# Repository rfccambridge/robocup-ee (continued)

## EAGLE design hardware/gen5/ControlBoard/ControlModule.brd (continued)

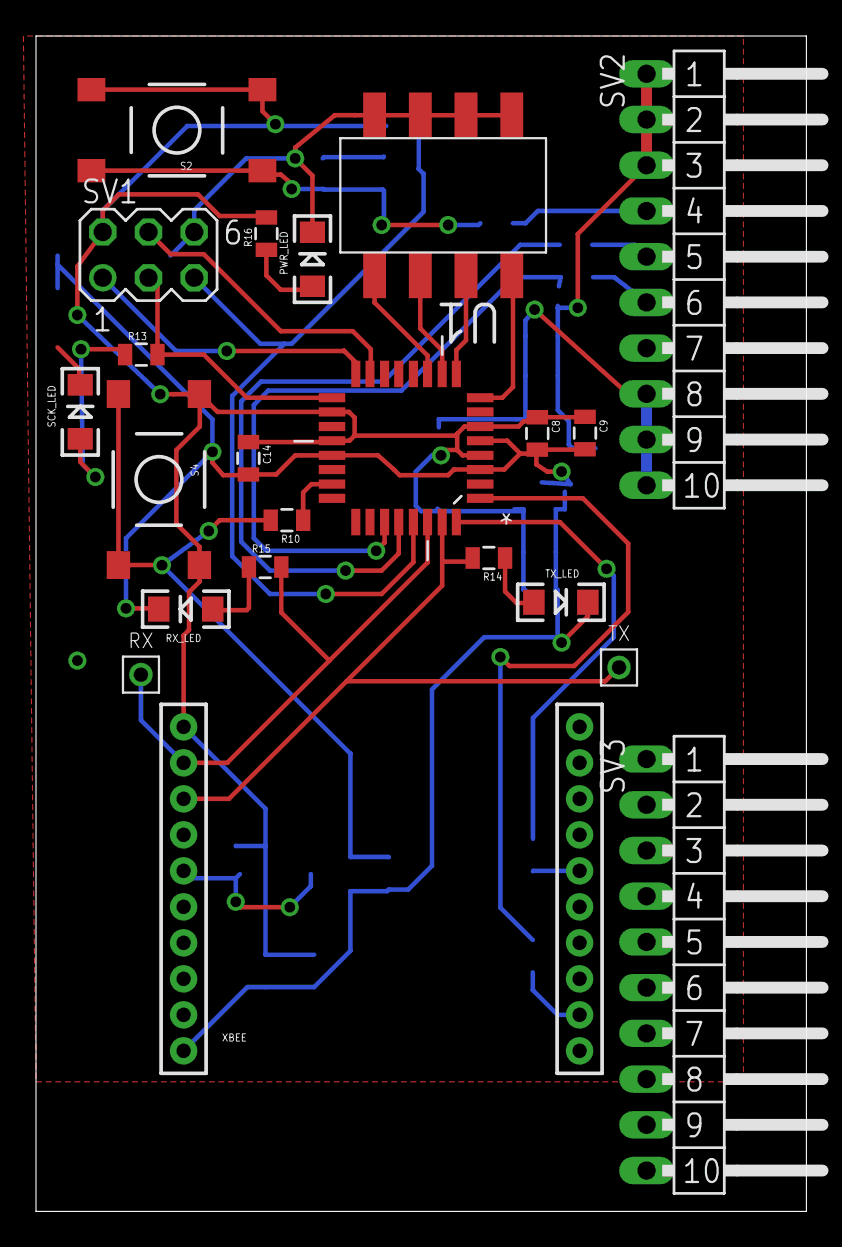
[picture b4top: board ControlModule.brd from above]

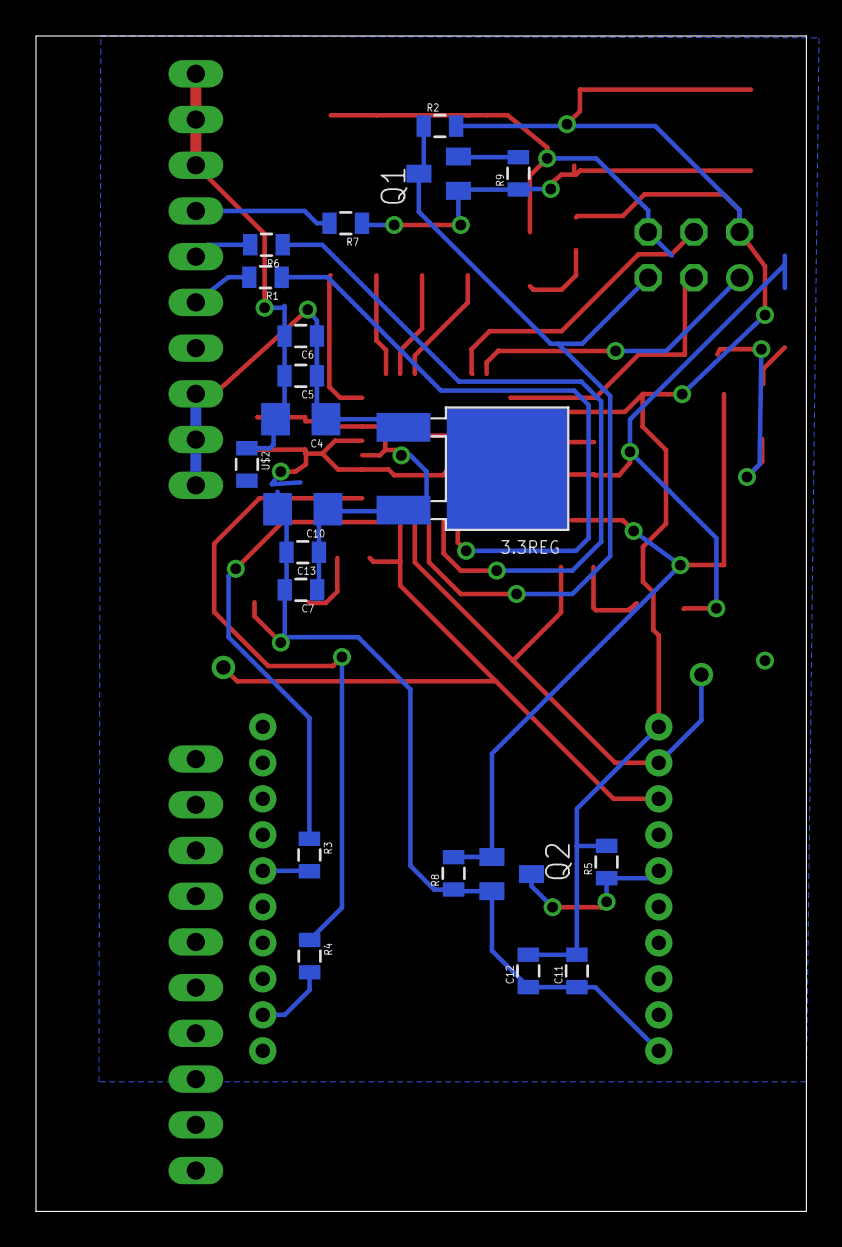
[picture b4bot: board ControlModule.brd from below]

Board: 2 copper layers, 42.8 x 65.3 mm, 44 parts (21 on the bottom side), 31 nets.

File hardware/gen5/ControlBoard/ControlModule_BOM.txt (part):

Partlist exported from C:/Users/joncr_000/robocup/robocup-ee/hardware/gen5/ControlBoard/ControlModule.sch at 12/26/2016 15:41:58

Part    Value         Device           Package               Description                                             MF MPN           OC_FARNELL OC_NEWARK PACKAGE PROD_ID    SUPPLIER VALUE        
3.3REG  3.3REG1AREG   3.3REG1AREG      DPAK                                                                                                                                                         
C4      47uF          CAP1206          1206                  Capacitor                                                                                                                              
C5      1uF           CAP0805          0805                  Capacitor                                                                                                                              
C6      0.01uF        CAP0805          0805                  Capacitor                                                                                                                              
C7      0.01uF        CAP0805          0805                  Capacitor                                                                                                                              
C8      10uF          CAP0805          0805                  Capacitor                                                                                                                              
C9      0.1uF         CAP0805          0805                  Capacitor                                                                                                                              
C10     47uF          CAP1206          1206                  Capacitor                                                                                                                              
C11     0.01uF        CAP0805          0805                  Capacitor                                                                                                                              
C12     1uF           CAP0805          0805                  Capacitor                                                                                                                              
C13     1uF           CAP0805          0805                  Capacitor                                                                                                                              
C14     0.1uF         CAP0805          0805                  Capacitor                                                                                                                              
FRAME1  FRAME-LETTER  FRAME-LETTER     CREATIVE_COMMONS      Schematic Frame                                                                                                                        
PWR_LED               LED1206          LED-1206              LEDs                                                                                                                                   
Q1      BSS123        BSS123           SOT23                 N-CHANNEL MOS FET                                                                                                                      
Q2      BSS123        BSS123           SOT23                 N-CHANNEL MOS FET                                                                                                                      
R1      100           RESISTOR0805-RES 0805                  Resistor                                                                                                                               
R2      10k           RESISTOR0805-RES 0805                  Resistor                                                                                                                               
R3      0             RESISTOR0805-RES 0805                  Resistor                                                                                                                               
R4      0             RESISTOR0805-RES 0805                  Resistor                                                                                                                               
R5      10k           RESISTOR0805-RES 0805                  Resistor                                                                                                                               
R6      100           RESISTOR0805-RES 0805                  Resistor                                                                                                                               
R7      100           RESISTOR0805-RES 0805                  Resistor                                                                                                                               
R8      10k           RESISTOR0805-RES 0805                  Resistor                                                                                                                               
R9      10k           RESISTOR0805-RES 0805                  Resistor                                                                                                                               
R10     100           RESISTOR0805-RES 0805                  Resistor                                                                                                                               
R13     1k            RESISTOR0805-RES 0805                  Resistor                                                                                                                               
R14     1k            RESISTOR0805-RES 0805                  Resistor                                                                                                                               
R15     1k            RESISTOR0805-RES 0805                  Resistor                                                                                                                               
R16     1k            RESISTOR0805-RES 0805                  Resistor                                                                                                                               
RX      TEST_PT       TEST_PT          TESTING_PT            Testing Point                                                                                                                          
RX_LED                LED1206          LED-1206              LEDs                                                                                                                                   
S2      TAC_SWITCHSMD TAC_SWITCHSMD    TACTILE-SWITCH-SMD    Momentary Switch                                                                                      SWCH-08247          TAC_SWITCHSMD
S4      TAC_SWITCHSMD TAC_SWITCHSMD    TACTILE-SWITCH-SMD    Momentary Switch                                                                                      SWCH-08247          TAC_SWITCHSMD
SCK_LED               LED1206          LED-1206              LEDs                                                                                                                                   
SV1     ICSP          MA03-2           MA03-2                PIN HEADER                                                               unknown    unknown                                            
SV2                   MA10-1W          MA10-1W               PIN HEADER                                                               unknown    unknown                                            
SV3                   MA10-1W          MA10-1W               PIN HEADER                                                               unknown    unknown                                            
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
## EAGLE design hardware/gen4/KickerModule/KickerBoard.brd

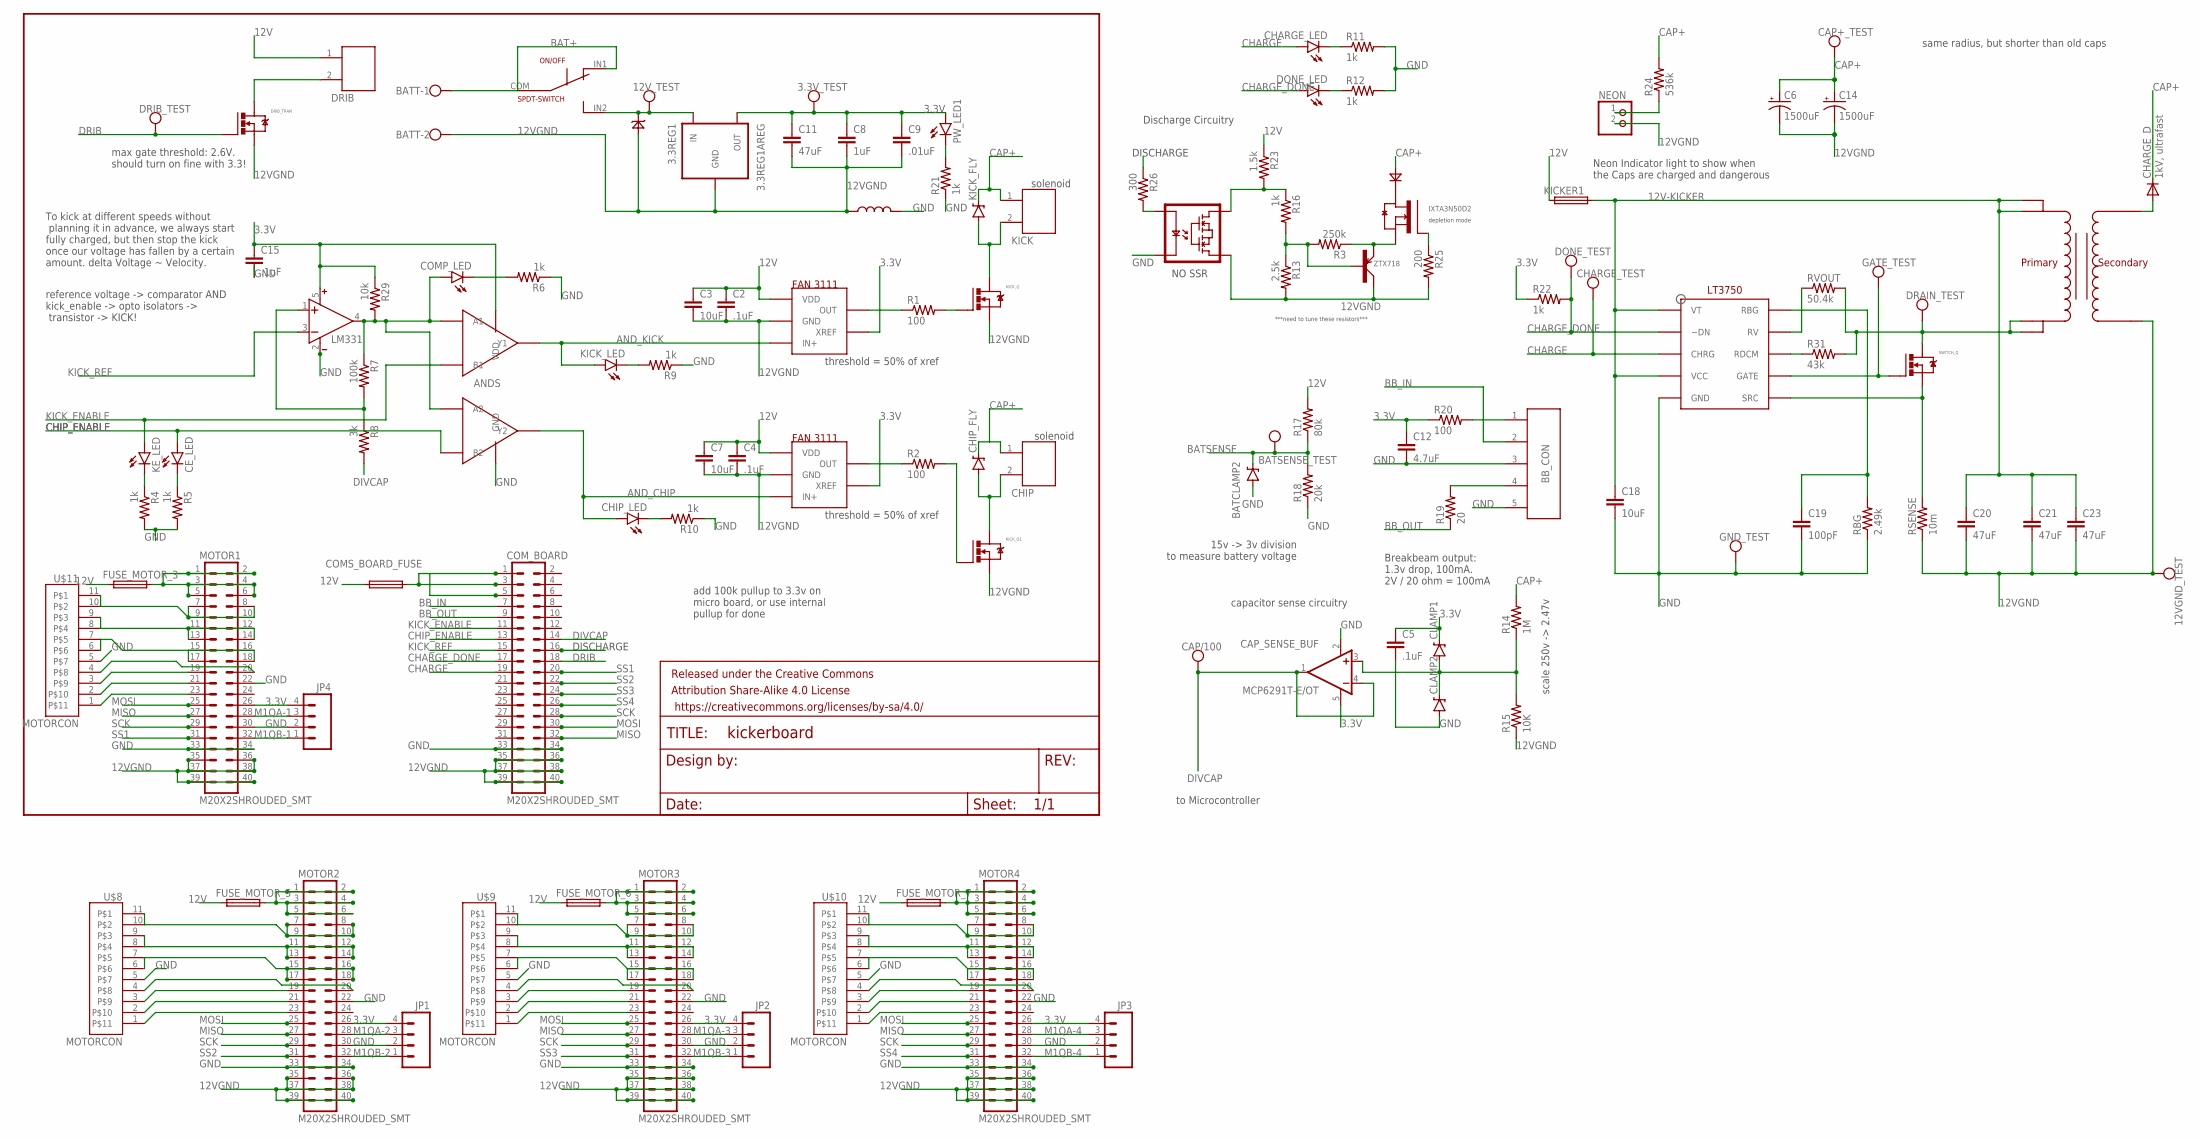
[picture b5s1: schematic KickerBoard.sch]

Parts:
3.3REG1: 3.3REG1AREG; DPAK
3.3V_TEST, 12VGND_TEST, 12V_TEST: TEST_PT; TESTING_PT
ANDS: AND-DUAL; TSSOP8
BATCLAMP2: DIODE-ZENERDO214AC; DO214AC
BATSENSE_TEST: TEST_PT; TESTING_PT
BATT: W237-102
BB_CON: JST-5; JST-5-2MM
C2, C4: .1uF; 1206
C3, C7: 10uF; 1206
C5, C15: .1uF; 0805
C6, C14: 1500uF; EB35D
C8: 1uF; 0805
C9: .01uF; 0805
C11, C20, C21, C23: 47uF; 1206
C12: 4.7uF; 0805
C18: 10uF; 0805
C19: 100pF; 0805
CAP+_TEST: TEST_PT; TESTING_PT
CAP/100: TEST_PT; TESTING_PT
CAP_COMP: LM331; SOT23-5
CAP_SENSE_BUF: MCP6291T-E/OT; SOT23-5
CE_LED: LED1206; LED-1206
CHARGE_D: 1kV, ultrafast; DO214AC
CHARGE_LED: LED1206; LED-1206
CHARGE_TEST: TEST_PT; TESTING_PT
CHARGE_U: LT3750; 10-MSOP
CHIP: JST-22MM; JST-2-2MM
CHIP_FLY: DIODE-ZENERDO214AB; DO214AB
CHIP_LED: LED1206; LED-1206
CLAMP1, CLAMP2: DIODE-ZENERDO214AC; DO214AC
COMP_LED: LED1206; LED-1206
COMS_BOARD_FUSE: TR5
COM_BOARD: M20X2SHROUDED_SMT; 2X20_SHROUDED_SMT
DONE_LED: LED1206; LED-1206
DONE_TEST: TEST_PT; TESTING_PT
DRAIN_TEST: TEST_PT; TESTING_PT
DRIB: JST-22MM; JST-2-2MM
DRIB_TEST: TEST_PT; TESTING_PT
DRIB_TRAN: N-MOSFETDPAK; DPAK
FRAME4: FRAME-LETTER; CREATIVE_COMMONS
FUSE_MOTOR_3, FUSE_MOTOR_5, FUSE_MOTOR_6, FUSE_MOTOR_7: TR5
GATE_TEST: TEST_PT; TESTING_PT
GND_TEST: TEST_PT; TESTING_PT
JP1, JP2, JP3, JP4: M04SMD_RA_FEMALE; 1X04_SMD_RA_FEMALE
KE_LED: LED1206; LED-1206
KICK: JST-22MM; JST-2-2MM
KICKER1: TR5
KICK_FLY: DIODE-ZENERDO214AB; DO214AB
KICK_LED: LED1206; LED-1206
KICK_Q, KICK_Q1: N-MOSFETDPAK; DPAK
MOTOR1, MOTOR2, MOTOR3, MOTOR4: M20X2SHROUDED_SMT; 2X20_SHROUDED_SMT
NEON: PINHD-1X2; 1X02
ON/OFF: SPDT-SWITCH; CK_SWITCH
PW_LED1: LED1206; LED-1206
R1, R2, R20: 100; 0805
R3: 250k; 0805
R4, R5, R6, R9, R10, R11, R12, R16, R21, R22: 1k; 0805
R7: 100k; 0805
R8: 3k; 0805
R13: 2.5k; 0805
R14: 1M; 0805
R15: 10K; 0805
R17: 80k; 0805
R18: 20k; 0805
R19: 20; 0805
R23: 1.5k; 0805
R24: 536k; 0805
R25: 200; 0805
R26: 300; 0805
R29: 10k; 0805
R31: 43k; 0805
RBG: 2.49k; 0805
RSENSE: 10m; R2512
RVOUT: 50.4k; 0805
SWITCH_Q: N-MOSFETDPAK; DPAK
U$1, U$4: FAN31111; SOT23-5
U$2: IXTA3N50D2; TO-263
U$3: 32052-TRANSFORMER; 10-TRANSFORMER
U$5: VO1400AEFTR; SOP4
U$6: ZTX718; TO92
U$7: 1N4007; THROUGH-HOLE-2
U$8, U$9, U$10, U$11: MOTORCON; GEN3CON
U$12: 13VZENER; THROUGH-HOLE-2
U$13: INDUCTOR; 0805

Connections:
3.3V: 3.3REG1.SOURCE (OUT), 3.3V_TEST.P$1, ANDS.P$8 (VDD), C5.1, C8.1, C9.1, C11.1, C12.1, C15.1, CAP_COMP.5 (V+), CAP_SENSE_BUF.5 (V+), CLAMP1.C, JP1.4, JP2.4, JP3.4, JP4.4, MOTOR1.26, MOTOR2.26, MOTOR3.26, MOTOR4.26, PW_LED1.A, R20.1, R22.1, R29.1, U$1.4 (XREF), U$4.4 (XREF)
12V: 3.3REG1.GATE (IN), 12V_TEST.P$1, C2.1, C3.1, C4.1, C7.1, COMS_BOARD_FUSE.1, DRIB.1, FUSE_MOTOR_3.1, FUSE_MOTOR_5.1, FUSE_MOTOR_6.1, FUSE_MOTOR_7.1, KICKER1.1, ON/OFF.IN2 (P2), R17.2, R23.1, U$1.1 (VDD), U$4.1 (VDD), U$12.-
12V-KICKER: C18.1, C20.1, C21.1, C23.1, CHARGE_U.P$1 (VT), CHARGE_U.P$4 (VCC), KICKER1.2, U$3.P$4, U$3.P$5
12VGND: 3.3REG1.DRAIN (GND), 12VGND_TEST.P$1, BATT.2, C2.2, C3.2, C4.2, C6.-, C7.2, C8.2, C9.2, C11.2, C14.-, C20.2, C21.2, C23.2, COM_BOARD.35, COM_BOARD.36, COM_BOARD.37, COM_BOARD.38, COM_BOARD.39, COM_BOARD.40, DRIB_TRAN.SOURCE (S), KICK_Q.SOURCE (S), KICK_Q1.SOURCE (S), MOTOR1.35, MOTOR1.36, MOTOR1.37, MOTOR1.38, MOTOR1.39, MOTOR1.40, MOTOR2.35, MOTOR2.36, MOTOR2.37, MOTOR2.38, MOTOR2.39, MOTOR2.40, MOTOR3.35, MOTOR3.36, MOTOR3.37, MOTOR3.38, MOTOR3.39, MOTOR3.40, MOTOR4.35, MOTOR4.36, MOTOR4.37, MOTOR4.38, MOTOR4.39, MOTOR4.40, NEON.2, R13.2, R15.1, R25.2, RSENSE.1, U$1.2 (GND), U$3.P$10, U$4.2 (GND), U$5.3 (S2), U$6.LEFT (COLLECTOR), U$12.+, U$13.1
AND_CHIP: ANDS.P$3 (Y2), CHIP_LED.A, U$1.3 (IN+)
AND_KICK: ANDS.P$7 (Y1), KICK_LED.A, U$4.3 (IN+)
BAT+: BATT.1, ON/OFF.COM, ON/OFF.IN1 (P1)
BATSENSE: BATCLAMP2.C, BATSENSE_TEST.P$1, R17.1, R18.2
BB_IN: BB_CON.2, COM_BOARD.7
BB_OUT: COM_BOARD.9, R19.1
CAP+: C6.+, C14.+, CAP+_TEST.P$1, CHARGE_D.C, CHIP.1, CHIP_FLY.CATHODE (C), KICK.1, KICK_FLY.CATHODE (C), R14.2, R24.2, U$7.+ (D+)
CHARGE: CHARGE_LED.A, CHARGE_TEST.P$1, CHARGE_U.P$3 (CHRG), COM_BOARD.19
CHARGE_DONE: CHARGE_U.P$2 (~DN), COM_BOARD.17, DONE_LED.A, DONE_TEST.P$1, R22.2
CHIP_ENABLE: ANDS.P$6 (B2), CE_LED.A, COM_BOARD.13
COMP_OUT: ANDS.P$1 (A1), ANDS.P$5 (A2), CAP_COMP.4 (OUT), COMP_LED.A, R7.1, R29.2
DISCHARGE: COM_BOARD.16, R26.1
DIVCAP: CAP/100.P$1, CAP_SENSE_BUF.1 (OUT), CAP_SENSE_BUF.4 (-IN), COM_BOARD.14, R8.2
DRIB: COM_BOARD.18, DRIB_TEST.P$1, DRIB_TRAN.GATE (G)
GND: ANDS.P$4 (GND), BATCLAMP2.A, BB_CON.3, BB_CON.5, C5.2, C12.2, C15.2, C18.2, C19.2, CAP_COMP.2 (V-), CAP_SENSE_BUF.2 (V-), CHARGE_U.P$5 (GND), CLAMP2.A, COM_BOARD.33, COM_BOARD.34, GND_TEST.P$1, JP1.2, JP2.2, JP3.2, JP4.2, MOTOR1.22, MOTOR1.30, MOTOR1.33, MOTOR1.34, MOTOR2.22, MOTOR2.30, MOTOR2.33, MOTOR2.34, MOTOR3.22, MOTOR3.30, MOTOR3.33, MOTOR3.34, MOTOR4.22, MOTOR4.30, MOTOR4.33, MOTOR4.34, R4.2, R5.2, R6.1, R9.1, R10.1, R11.2, R12.2, R18.1, R21.1, RBG.1, U$5.2 (LED-), U$8.5, U$9.5, U$10.5, U$11.5, U$13.2
HYSTERESIS: CAP_COMP.1 (IN+), R7.2, R8.1
KICK_ENABLE: ANDS.P$2 (B1), COM_BOARD.11, KE_LED.A
KICK_REF: CAP_COMP.3 (IN-), COM_BOARD.15
LOWCHIP: CHIP.2, CHIP_FLY.ANODE (A), KICK_Q1.DRAIN (D)
LOWKICK: KICK.2, KICK_FLY.ANODE (A), KICK_Q.DRAIN (D)
M1QA-1: JP4.3, MOTOR1.28
M1QA-2: JP1.3, MOTOR2.28
M1QA-3: JP2.3, MOTOR3.28
M1QA-4: JP3.3, MOTOR4.28
M1QB-1: JP4.1, MOTOR1.32
M1QB-2: JP1.1, MOTOR2.32
M1QB-3: JP2.1, MOTOR3.32
M1QB-4: JP3.1, MOTOR4.32
MISO: COM_BOARD.32, MOTOR1.27, MOTOR2.27, MOTOR3.27, MOTOR4.27
MOSI: COM_BOARD.30, MOTOR1.25, MOTOR2.25, MOTOR3.25, MOTOR4.25
unnamed: DRAIN_TEST.P$1, R31.2, RVOUT.2, SWITCH_Q.DRAIN (D), U$3.P$6, U$3.P$7
unnamed: R1.1, U$4.5 (OUT)
unnamed: KICK_Q1.GATE (G), R2.2
unnamed: FUSE_MOTOR_6.2, MOTOR3.1, MOTOR3.2, MOTOR3.3, MOTOR3.4, MOTOR3.5, MOTOR3.6
unnamed: R2.1, U$1.5 (OUT)
unnamed: CHARGE_U.P$8 (RDCM), R31.1
unnamed: C19.1, CHARGE_U.P$10 (RBG), RBG.2
unnamed: KICK_Q.GATE (G), R1.2
unnamed: CHARGE_U.P$7 (GATE), GATE_TEST.P$1, SWITCH_Q.GATE (G)
unnamed: R3.1, U$2.LOWER_RIGHT (SOURCE), U$6.RIGHT (EMITTER)
unnamed: KE_LED.C, R4.1
unnamed: CHARGE_U.P$9 (RV), RVOUT.1
unnamed: CE_LED.C, R5.1
unnamed: COMP_LED.C, R6.2
unnamed: KICK_LED.C, R9.2
unnamed: CHIP_LED.C, R10.2
unnamed: R3.2, R13.1, R16.2, U$6.CENTER (BASE)
unnamed: DONE_LED.C, R12.1
unnamed: CHARGE_LED.C, R11.1
unnamed: R25.1, U$2.LOWER_LEFT (GATE)
unnamed: PW_LED1.C, R21.2
unnamed: CHARGE_U.P$6 (SRC), RSENSE.2, SWITCH_Q.SOURCE (S)
unnamed: FUSE_MOTOR_7.2, MOTOR4.1, MOTOR4.2, MOTOR4.3, MOTOR4.4, MOTOR4.5, MOTOR4.6
unnamed: FUSE_MOTOR_5.2, MOTOR2.1, MOTOR2.2, MOTOR2.3, MOTOR2.4, MOTOR2.5, MOTOR2.6
unnamed: FUSE_MOTOR_3.2, MOTOR1.1, MOTOR1.2, MOTOR1.3, MOTOR1.4, MOTOR1.5, MOTOR1.6
unnamed: COMS_BOARD_FUSE.2, COM_BOARD.1, COM_BOARD.3, COM_BOARD.5
unnamed: R16.1, R23.2, U$5.4 (S1)
unnamed: R26.2, U$5.1 (LED+)
unnamed: BB_CON.4, R19.2
unnamed: U$2.TAB (DRAIN), U$7.- (D-)
unnamed: MOTOR2.7, MOTOR2.8, MOTOR2.9, MOTOR2.10, U$8.10, U$8.11
unnamed: MOTOR2.11, MOTOR2.12, MOTOR2.13, MOTOR2.14, U$8.8, U$8.9
unnamed: MOTOR2.15, MOTOR2.16, MOTOR2.17, MOTOR2.18, U$8.6, U$8.7
unnamed: BB_CON.1, R20.2
unnamed: MOTOR2.20, U$8.4
unnamed: MOTOR2.19, U$8.3
unnamed: MOTOR2.21, U$8.2
unnamed: MOTOR2.23, U$8.1
unnamed: MOTOR1.7, MOTOR1.8, MOTOR1.9, MOTOR1.10, U$11.10, U$11.11
unnamed: MOTOR1.11, MOTOR1.12, MOTOR1.13, MOTOR1.14, U$11.8, U$11.9
unnamed: MOTOR1.15, MOTOR1.16, MOTOR1.17, MOTOR1.18, U$11.6, U$11.7
unnamed: MOTOR1.20, U$11.4
unnamed: MOTOR1.19, U$11.3
unnamed: MOTOR1.21, U$11.2
unnamed: MOTOR1.23, U$11.1
unnamed: MOTOR3.7, MOTOR3.8, MOTOR3.9, MOTOR3.10, U$9.10, U$9.11
unnamed: MOTOR3.11, MOTOR3.12, MOTOR3.13, MOTOR3.14, U$9.8, U$9.9
unnamed: MOTOR3.15, MOTOR3.16, MOTOR3.17, MOTOR3.18, U$9.6, U$9.7
unnamed: MOTOR3.20, U$9.4
unnamed: MOTOR3.19, U$9.3
unnamed: MOTOR3.21, U$9.2
unnamed: MOTOR3.23, U$9.1
unnamed: MOTOR4.7, MOTOR4.8, MOTOR4.9, MOTOR4.10, U$10.10, U$10.11
unnamed: MOTOR4.11, MOTOR4.12, MOTOR4.13, MOTOR4.14, U$10.8, U$10.9
unnamed: MOTOR4.15, MOTOR4.16, MOTOR4.17, MOTOR4.18, U$10.6, U$10.7
unnamed: MOTOR4.20, U$10.4
unnamed: MOTOR4.19, U$10.3
unnamed: MOTOR4.21, U$10.2
unnamed: MOTOR4.23, U$10.1
SCK: COM_BOARD.28, MOTOR1.29, MOTOR2.29, MOTOR3.29, MOTOR4.29
SS1: COM_BOARD.20, MOTOR1.31
SS2: COM_BOARD.22, MOTOR2.31
SS3: COM_BOARD.24, MOTOR3.31
SS4: COM_BOARD.26, MOTOR4.31
TO_DRIB: DRIB.2, DRIB_TRAN.DRAIN (D)
TO_NEON: NEON.1, R24.1
TRANS_OUT: CHARGE_D.A, U$3.P$1
UNBUF_DIVCAP: CAP_SENSE_BUF.3 (+IN), CLAMP1.A, CLAMP2.C, R14.1, R15.2

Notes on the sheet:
scale 250v -> 2.47v
To kick at different speeds without planning it in advance, we always start fully charged, but then stop the kick once our voltage has fallen by a certain amount. delta Voltage ~ Velocity.
reference voltage -> comparator AND kick_enable -> opto isolators -> transistor -> KICK!
add 100k pullup to 3.3v on micro board, or use internal pullup for done
Neon Indicator light to show when the Caps are charged and dangerous
to Microcontroller
threshold = 50% of xref
same radius, but shorter than old caps
Discharge Circuitry
capacitor sense circuitry
15v -> 3v division to measure battery voltage
max gate threshold: 2.6V. should turn on fine with 3.3!
Breakbeam output: 1.3v drop, 100mA. 2V / 20 ohm = 100mA
solenoid
DISCHARGE
IXTA3N50D2
ZTX718
***need to tune these resistors***
depletion mode
NO SSR

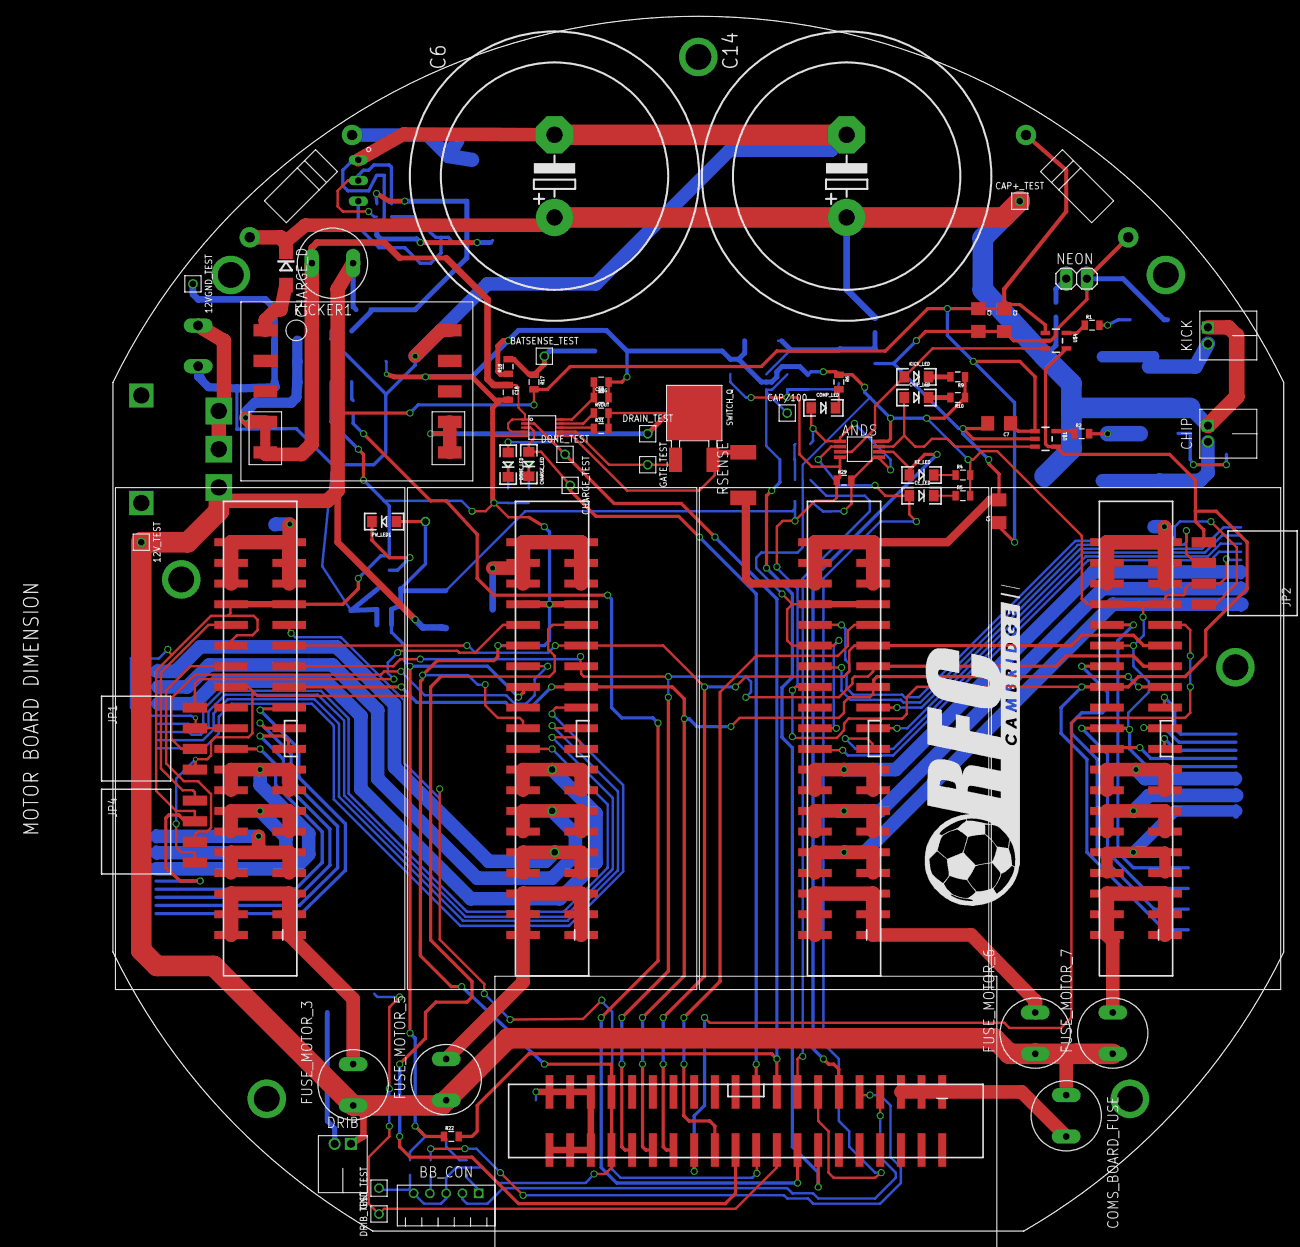
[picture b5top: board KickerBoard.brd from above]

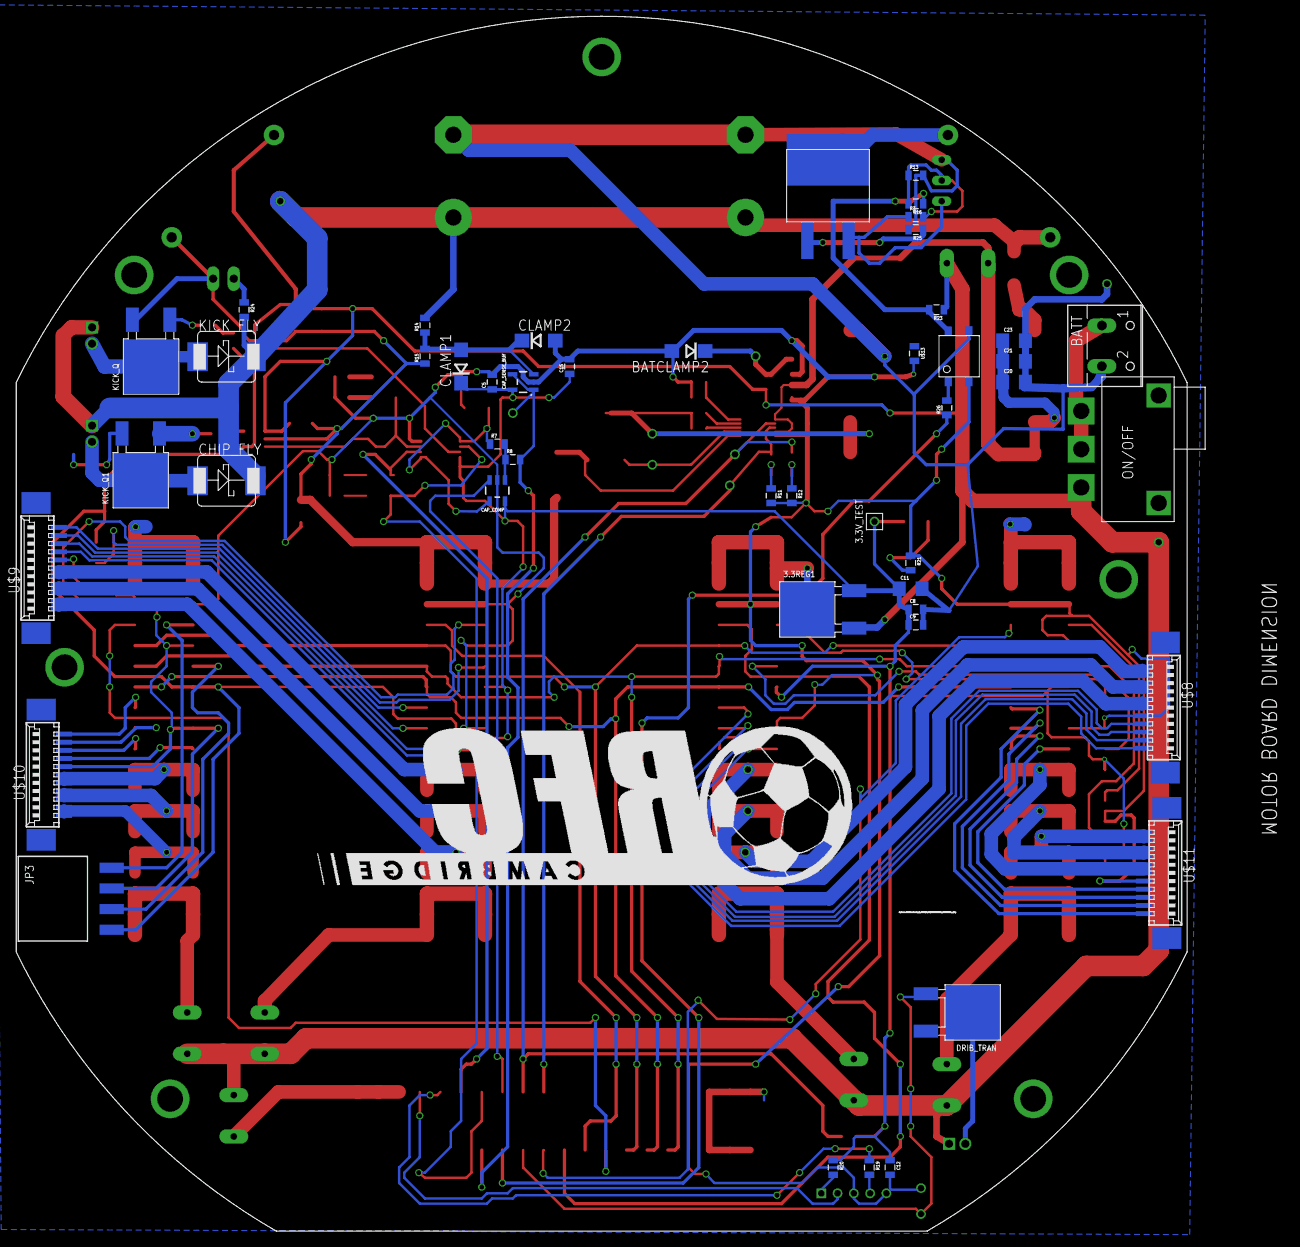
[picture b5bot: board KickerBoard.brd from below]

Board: 2 copper layers, 143.9 x 149.3 mm, 119 parts (47 on the bottom side), 102 nets.

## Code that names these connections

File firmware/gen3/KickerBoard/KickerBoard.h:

#include "EELib.h"

#define CHARGE_LIMIT 0.0

// Pin names
pin_def CHARGE = pin_def(&PORTA, 0);
pin_def DISCHARGE = pin_def(&PORTA, 1);
pin_def KICK_ENABLE = pin_def(&PORTA, 2);
pin_def CHIP_ENABLE = pin_def(&PORTA, 3);
pin_def DONE = pin_def(&PORTA, 4);

pin_def SS_K = pin_def(&PINB, 0);
pin_def SCK = pin_def(&PINB, 1);
pin_def MOSI = pin_def(&PINB, 2);
pin_def MISO = pin_def(&PORTB, 3);

pin_def KICK_PWM = pin_def(&PORTB, 5);
pin_def DRIB = pin_def(&PORTB, 6);
pin_def BB_OUT = pin_def(&PORTB, 7);

pin_def RLED1 = pin_def(&PORTC, 1);
pin_def RLED2 = pin_def(&PORTC, 2);
pin_def BLED1 = pin_def(&PORTC, 3);
pin_def BLED2 = pin_def(&PORTC, 4);
pin_def GLED1 = pin_def(&PORTC, 5);
pin_def GLED2 = pin_def(&PORTC, 6);

pin_def DIVCAP = pin_def(&PINF, 0);
pin_def BATSENSE = pin_def(&PINF, 1);
pin_def BB_IN = pin_def(&PINF, 2);

pin_def RESET = pin_def(&PING, 5);

int main();
int processCommand(Command &command);
void handleKickCommand(KickCommand &command);
void handleChargeCommand(ChargeCommand &command);

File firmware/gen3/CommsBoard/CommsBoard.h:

#include "EELib.h"

// Pin names
pin_def BID3 = pin_def(&PINA, 0);
pin_def BID2 = pin_def(&PINA, 1);
pin_def BID1 = pin_def(&PINA, 2);
pin_def BID0 = pin_def(&PINA, 3);

// returns robot ID from first half of pin A
// damn it have to reverse order
char getBotID() {
	return (0x0F & (reverse(PINA) >> 4));
}

pin_def EX3 = pin_def(&PINA, 4);
pin_def EX2 = pin_def(&PINA, 5);
pin_def EX1 = pin_def(&PINA, 6);
pin_def EX0 = pin_def(&PINA, 7);

pin_def SCK = pin_def(&PINB, 1);
pin_def MOSI = pin_def(&PINB, 2);
pin_def MISO = pin_def(&PORTB, 3);

pin_def RLED1 = pin_def(&PORTC, 0);
pin_def RLED2 = pin_def(&PORTC, 1);
pin_def BLED1 = pin_def(&PORTC, 2);
pin_def BLED2 = pin_def(&PORTC, 3);
pin_def GLED1 = pin_def(&PORTC, 4);
pin_def GLED2 = pin_def(&PORTC, 5);
pin_def YLED1 = pin_def(&PORTC, 6);
pin_def YLED2 = pin_def(&PORTC, 7);

pin_def SPARE1 = pin_def(&PORTD, 0);
pin_def SPARE2 = pin_def(&PORTD, 1);
pin_def SPARE3 = pin_def(&PORTD, 2);
pin_def SPARE4 = pin_def(&PORTD, 3);
pin_def SPARE5 = pin_def(&PORTD, 4);

pin_def RX = pin_def(&PORTE, 0);
pin_def TX = pin_def(&PORTE, 1);
pin_def XBRST = pin_def(&PORTE, 2);
pin_def INT = pin_def(&PORTE, 3);
pin_def SCL = pin_def(&PORTE, 4);
pin_def SDA = pin_def(&PORTE, 5);
pin_def RTS = pin_def(&PORTE, 6);
pin_def CTS = pin_def(&PORTE, 7);

pin_def SS_M = pin_def(&PORTF, 0);
pin_def SS_K = pin_def(&PORTF, 1);
pin_def SS_E1 = pin_def(&PORTF, 2);
pin_def SS_E2 = pin_def(&PORTF, 3);
pin_def SS_E3 = pin_def(&PORTF, 4);
pin_def SS_E4 = pin_def(&PORTF, 5);
pin_def SS_E5 = pin_def(&PORTF, 6);
pin_def TSENSE = pin_def(&PINF, 7);

pin_def RESET = pin_def(&PING, 5);

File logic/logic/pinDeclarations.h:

/*************************************************************************
* Defines                                                                *  
**************************************************************************/

// software settable address
#define ADDRESS 3

// motor direction control pins (swapped to accomodate f'ed up electronics, setMotorFunc also swapped)
#define M0DIR PORTBbits.RB5
#define M1DIR PORTBbits.RB0
#define M2DIR PORTBbits.RB2
#define M3DIR PORTBbits.RB6

// brake pins (Low true: ie. 0V == brake) (not swapped)
#define BRAKE0 PORTDbits.RD4
#define BRAKE1 PORTDbits.RD6
#define BRAKE2 PORTDbits.RD5
#define BRAKE3 PORTCbits.RC5

// LED pins
#define LED0 PORTDbits.RD0
#define LED1 PORTDbits.RD1
#define LED2 PORTDbits.RD2
#define LED3 PORTDbits.RD3

// other pins
#define KICK PORTAbits.RA6
#define CHIP PORTCbits.RC1
#define CHARGE PORTEbits.RE1
#define DISCHARGE PORTEbits.RE0
#define DRIBBLER_DIR PORTCbits.RC3
#define BALL_DETECT PORTCbits.RC4 // this one is an input

// serial pins 
#define TX_EN PORTEbits.RE2

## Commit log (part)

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2016-02-13 messing with layout, still need header pin info
2016-02-13 cleaned things up a bit, extended board
2016-02-13 Revert "fixed overlaps, nearly finished routing"
    This reverts commit 58b1fdd4e09a09fd026863b48e748c651eb8a543.
2016-02-13 Add some kicker/mother board layout.
2016-02-20 Main board work in progress
    bc jon wanted me to push
2016-02-21 Added test points
    Placed test point + overlap errors
2016-02-27 fix consistency error
2016-02-28 Add SPI pins to board headers and rename old "done" pins.
2016-03-05 Began BOM for Controls
2016-03-19 motor board redesign
    redesigned the motor board, with fever clearance / overlap issues,
    overall just moved around components.
2016-03-19 layout on mainboard
    layout on mainboard almost done.
2016-03-27 updated connectors
2016-03-31 motor board almost done
    motor board almost done and also mainboard
2016-03-31 motor board v2 done
    things to do, address clearance and maybe change min trace width
2016-03-31 added new discharge circuit - spruced up for design review
2016-04-01 added power resistor to library
2016-04-01 added name and value to device
2016-04-02 added opto-isolator part for discharge circuit
2016-04-02 testing git: added fubar
2016-04-02 testing with new file
2016-04-02 updated hello file
2016-04-02 more hello changes
2016-04-02 *careless whisper plays softly in the background*
2016-04-02 gitstuff
2016-04-03 finished routing... still need to do error checking
2016-04-04 cleaned up a few things
2016-04-09 motor board fix
    final changes
2016-04-10 motor and kicker fixes
2016-04-10 more preliminary placement
2016-04-10 passes erc
2016-04-11 main board in progress - about two thirds
2016-04-11 main board done - needs review
2016-04-11 changed up ground planes
2016-04-12 fixed overlaps
2016-04-13 more gerber files. also all orders went through (technically)
2016-04-16 added eagle BOMs
2016-05-07 added testing firmware directory
2016-05-08 Add XBee-controlled LED demo for comms board.
2016-05-16 starting routing
    done layout
2016-05-16 routing in progress (comms board)
2016-05-17 routing comms board done
2016-05-17 updated auto discharge - need manual discharge
2016-05-17 discharge circuit improved in schematic
2016-05-18 comms board done I think
2016-05-18 pdi fix
2016-05-18 redid debug connector on comms, but clearance checks havent been done
2016-05-19 more changes
2016-05-19 comms board conditionally done - still needs work
2016-05-19 values for discharge circuitry for now
2016-05-22 fixed connector pins
    changed spi pins to have shorter runs.
2016-05-22 changes to motor and main board
2016-05-22 push button fix
2016-05-23 motor board push button fix
2016-05-23 fixed all clearance issues on motorboard, stop mask still to go
2016-05-23 changed cap value on motorboard (CP1 and CP2)
2016-05-23 extra motor pins
2016-05-23 extended motor controller pads
2016-05-23 added motorconnector to mainboard
2016-05-24 comms passes drc this was exhausting
2016-05-24 fixed minor detail about capacitor sizes (using 0.01uF everywhere instead of .01uF on comms)
2016-05-25 motorboard ground connections fixes
2016-05-25 an experiment with ground connections on motorboard - reverse if necessary
2016-05-25 finished increasing trace width on motorboard
2016-05-25 new sizes + fixes
2016-05-26 added library parts
2016-05-26 added ferrite beads
2016-05-26 new shape
2016-05-26 new shape part2
2016-05-27 routing in progress
2016-05-27 mainboard done w errors
2016-05-27 few fixes
2016-05-29 Panelizing
2016-05-30 new gerbers
2016-05-31 gerber fix
2016-06-01 dimension fixes
2016-09-25 adding workspace
2016-09-25 testing catkin
2016-09-25 made new ws
2016-09-27 changed project folder
2016-09-27 Added some comments
2016-09-29 Added update duty cycle functionality; still planning to do some testing on that later
2016-09-30 So this worked, but not when I restarted microcontroller.... hmmm...
2016-10-09 added a visualization example e package using_markers
2016-10-09 added ability to place lines in rviz
2016-10-09 Streamlined Build Environment Setup
2016-10-22 added gen5 hardware directory
2016-10-22 minor change
2016-10-23 added new motherboard directory, starting to integrate new MCU in
2016-10-23 added include to basic shapes
2016-10-24 Basics of the kicker module completed. Still need to add kick enable and chip enable functionality.
2016-10-24 minor changes
2016-10-25 forgot to git add the new msg/srv directories
2016-10-28 Established a solid code base
2016-10-28 Move cube based on incoming position messages
2016-10-30 WASD moving ball
2016-11-05 Prettied up code
2016-11-05 Added gen5 control board files
2016-11-05 deleted unneccessary signals
2016-11-06 added AND gate to mainboard. This is used to determine if a motor is faulting, in which case we should stop all motors.
2016-11-06 added file for KickerBoard.brd
2016-11-08 adding motherboard BOM
2016-11-13 updated message file
2016-11-17 change comparator to LM311 on motherboard due to conflicting information in the datasheet of the old part, the LM331
2016-11-18 Began Motherboard Layout!
2016-11-18 Integrated get position service with all instantiated cube instances
2016-11-18 All parts are not placed on the main board... not to do the traces
2016-11-19 basic PID controlle implementation complete. We can talk about how to improve the design and model during our meeting this weekend
2016-11-20 More progress on the motherboard layout
2016-11-20 Changed object to cylinder
2016-11-20 Tidied code up a bit
2016-11-21 Finishing up layout out traces for MCU on Motherboard
2016-11-22 Made congregated constants file
2016-11-24 Started work on cube scalability
2016-11-24 Abstracting publisher to `CubeInterface`
2016-11-25 Motherboard progress
2016-11-26 finished control module - needs review - might need more condensing?
2016-11-27 Added better error logging
2016-12-01 added to the BOM
2016-12-01 Motherboard Layout needs review, design rule checking, and new header for comms board. Other than that, the layout is done.
2016-12-04 comms board
2016-12-12 debugging static function declaration stuff in new game class
2016-12-13 Added the appropriate headers to the mother board
2016-12-13 small fix to control module gnd
2016-12-13 small change
2016-12-16 code compiles
2016-12-17 added new game files
2016-12-17 Implemented clang-formatter over C++ code
2016-12-17 Formatter set and new code architecture compiles and works
2016-12-20 Added correct border +small fixes
    Added correct border
    Added logo
    Fixed one large capacitor had a very thin wire connecting it to the
    other one.
    Added mounting holes
    NO more clearance errors
2016-12-20 removed extra part
    removed extra part
2016-12-20 Implemented ball and abstracted marker type
2016-12-21 almost completed the motherboard BOM
2016-12-22 Working on motor board layout - should be done soon
2016-12-23 few minor motor board fixes
2016-12-23 fixed an accidental change to main board
2016-12-23 Specified `getMarkerIdentity` function in `CustomMarker`
2016-12-26 Renamed all cubes and cube related code to more meaningful names
2016-12-26 Working on BOMs for motor and comms boards
2016-12-28 All board BOMs finished
2017-01-06 added pullups to the motorboard, and did DRC checking
2017-01-11 added comms board gerbers
2017-01-11 added motorboard gerbers, but noticed some potential issues with grounding afterwards. Checking into it now. It appears that the commsboard is ready to go, however
2017-01-13 connected plane to gnd and straightened out board outlines
2017-01-29 Added motor pin functionality
2017-01-29 working on xbee + ROS comms firmware
2017-01-29 added ros files to project
2017-01-29 added a file i missed
2017-01-29 updating ros files
2017-02-01 Completed python brain
2017-02-02 Fixed issue with CMakeLists file. Project should now compile. Run catkin_make install to install python files. You may have to make them executable with chmod +x brain.py
2017-02-02 completed improved kicker chip layout
2017-02-04 beginning motherboard revisions
2017-02-13 I just wanted to clean up a couple files in the firmware for easier use later. Excited to get these robots rollin.
2017-02-13 added pin.h file to repo
2017-03-03 added functionality to allow marker rotations in rviz using quaternion operations. See the function rotate_marker in Game.h.
2017-03-04 added two more files
2017-03-05 added some code in spin that models the robot's dynamics
2017-03-07 added functionality to service server that allows us to report the current pose of the robot in radians. Still need to perform velocity vector transformations on the python side, however.
2017-03-08 Added IO-Expander to schematic. Need others to review before others begin to work on layout, and completing other aspects of the revision
2017-03-24 updating board
2017-03-24 more progress
2017-03-25 Added V dividers with buffers
2017-03-26 swapped motorboard traces for hallout signals
2017-03-26 Here, John
2017-03-27 Revert "for lev and daniel"
    This reverts commit 2ad717e832d237175bcf1ebd5d5df5283078cebd.
2017-03-27 Right Multiplexer Fully Installed
2017-03-27 made smaller drill holes
2017-03-27 added two more wires to left multiplexer
2017-03-31 improved ground connections near left side motor, added 5V regulator,comms i2c lines, and cleaned up a bit. Almost there
2017-04-02 Voltage Dividers Installed
2017-04-07 finishing
2017-04-09 added grass to field and moved constants to shared code
2017-04-13 done
2017-04-13 added circle to field
2017-04-16 trying to add nonactive marker field
2017-04-23 SHIEBER SLKDJFLKSDJFL:KSDJF:LKSDJF:LKDSJFL:KSDJF:LKDSJF:LKSDJF:LKSDJF:LKDSJF:LKDJF:LKSDJF:LKDJF:LKDSJF:LKSDJF:LKSDJF:LKDSJF:LKSDJF:LSDKFJ:LSKDFJ:SDLKFJDS:KLFJDSK:LJF:KLSDJF:LSDKJFDKLS:J
2017-04-23 added field_lines.stl
2017-05-12 Small changes to TWI constants and such
2017-09-16 Restructured Motor Module and PWM firmware
2017-09-23 avoidance of ball
2017-09-28 made a new catkin_ws??
2017-10-07 layers
2017-10-07 added middle layer ripup
2017-10-13 12V+ connectors added
2017-11-10 miles v1
    ripped up some dangling wires, 12 V board, rats nested to layer.
2017-11-10 Added I2C and SPI headers, still need to route traces
2017-11-12 replaced motor connectors, still need to be routed
2018-01-22 Removed unnecessary power busses since transition to 4 layer board. Added Teensy to board and started placement. Time to eat
2018-01-29 Added new motorboard connectors to the motherboard and cleaned up old stuff
2018-01-31 small motherboard changes
2018-01-31 starting to re-write motorboard
2018-02-03 fixing merge conflicts
2018-02-03 added power connector to library and motorboard
2018-02-03 placement ok - started rrouting
2018-02-07 routing progress on motherboard
2018-02-07 re-routed 3.3V bus
2018-02-10 reformatted motherboard schematic into functional blocks
2018-02-10 motor
    motor part
2018-02-10 routed, needs cleanup
2018-02-11 more routing nearly there
2018-02-11 more routing
2018-02-12 finished routing no errors
2018-02-12 add motorboard as a part and finsihed all routing, no more 'ignoreable issues'
2018-02-12 added motorboard part to motherboard
2018-03-14 motor connector adapter
2018-10-13 made gen6 folder
2018-10-13 created gen6
2018-10-17 finished beginnings of schematic
2018-10-18 rotating the entire center piece
2018-10-24 back up without rotation
2018-10-25 added VNH5019A-E package to schematic
2018-10-27 dealt with J7, J1, and Q1
2018-10-27 wiring board 50 percent donegit add hardware/gen5/MotherBoard/KickerBoard2.0.brd !
2018-10-27 oh dear lord
2018-10-27 added library
2018-11-10 moved connector to edge, replaced transistors, routed
2019-02-02 new motor controller
2019-02-02 new motor controller2
2019-02-04 almost done2
2019-02-13 clean up and bom
2019-09-20 new-small board
2020-10-14 Changing to 3.3V
2021-04-08 bldc com, pwm clk divider
2021-04-15 fixing bugs with testbenches
